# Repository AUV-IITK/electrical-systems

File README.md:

# electrical-systems
# PURPOSE
The boost converter is Dc to Dc step up volatage while stepping dowm current. It is mainly used to reduce the voltage ripples in the input side(battery) to produce constant Dc output.
# SPECS
- Input Voltage range-14.8 to 16.8 volts
- DC output-19 volts
- output current- 3A
- Ambient Temp-30degree Centigrade
- base_pn-TPS55340-Q1

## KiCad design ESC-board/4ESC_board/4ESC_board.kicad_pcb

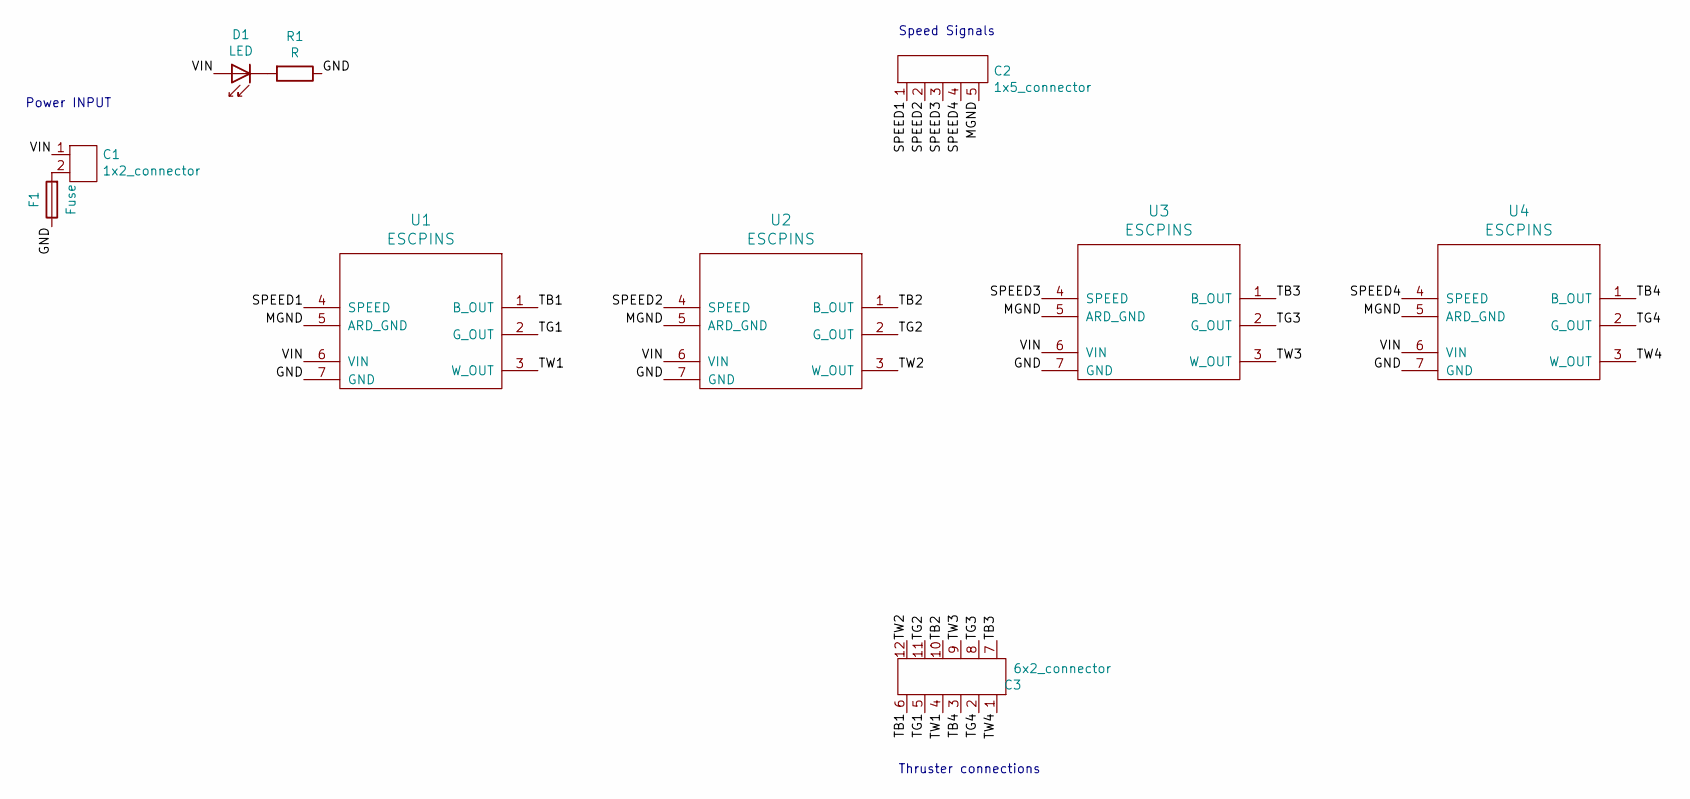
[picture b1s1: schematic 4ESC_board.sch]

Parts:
C1: 1x2_connector; molex_supersabre_1x2_172043-0201
C2: 1x5_connector; Molex_Microfit_1x5_436500500
C3: 6x2_connector; Molex_microfit_2x6_444281201
D1: LED; D_1206_3216Metric_Pad1.42x1.75mm_HandSolder
F1: Fuse; MCCQ-122
R1: R; R_1206_3216Metric_Pad1.42x1.75mm_HandSolder
U1, U2, U3, U4: ESCPINS; ESC_footprint

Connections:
/GND: F1.1, R1.1, U1.7 (GND), U2.7 (GND), U3.7 (GND), U4.7 (GND)
/MGND: C2.5, U1.5 (ARD_GND), U2.5 (ARD_GND), U3.5 (ARD_GND), U4.5 (ARD_GND)
/SPEED1: C2.1, U1.4 (SPEED)
/SPEED2: C2.2, U2.4 (SPEED)
/SPEED3: C2.3, U3.4 (SPEED)
/SPEED4: C2.4, U4.4 (SPEED)
/TB1: C3.6, U1.1 (B_OUT)
/TB2: C3.10, U2.1 (B_OUT)
/TB3: C3.7, U3.1 (B_OUT)
/TB4: C3.3, U4.1 (B_OUT)
/TG1: C3.5, U1.2 (G_OUT)
/TG2: C3.11, U2.2 (G_OUT)
/TG3: C3.8, U3.2 (G_OUT)
/TG4: C3.2, U4.2 (G_OUT)
/TW1: C3.4, U1.3 (W_OUT)
/TW2: C3.12, U2.3 (W_OUT)
/TW3: C3.9, U3.3 (W_OUT)
/TW4: C3.1, U4.3 (W_OUT)
/VIN: C1.1, D1.2 (A), U1.6 (VIN), U2.6 (VIN), U3.6 (VIN), U4.6 (VIN)
unnamed: C1.2, F1.2
unnamed: D1.1 (K), R1.2

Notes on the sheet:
Power INPUT
Speed Signals
Thruster connections

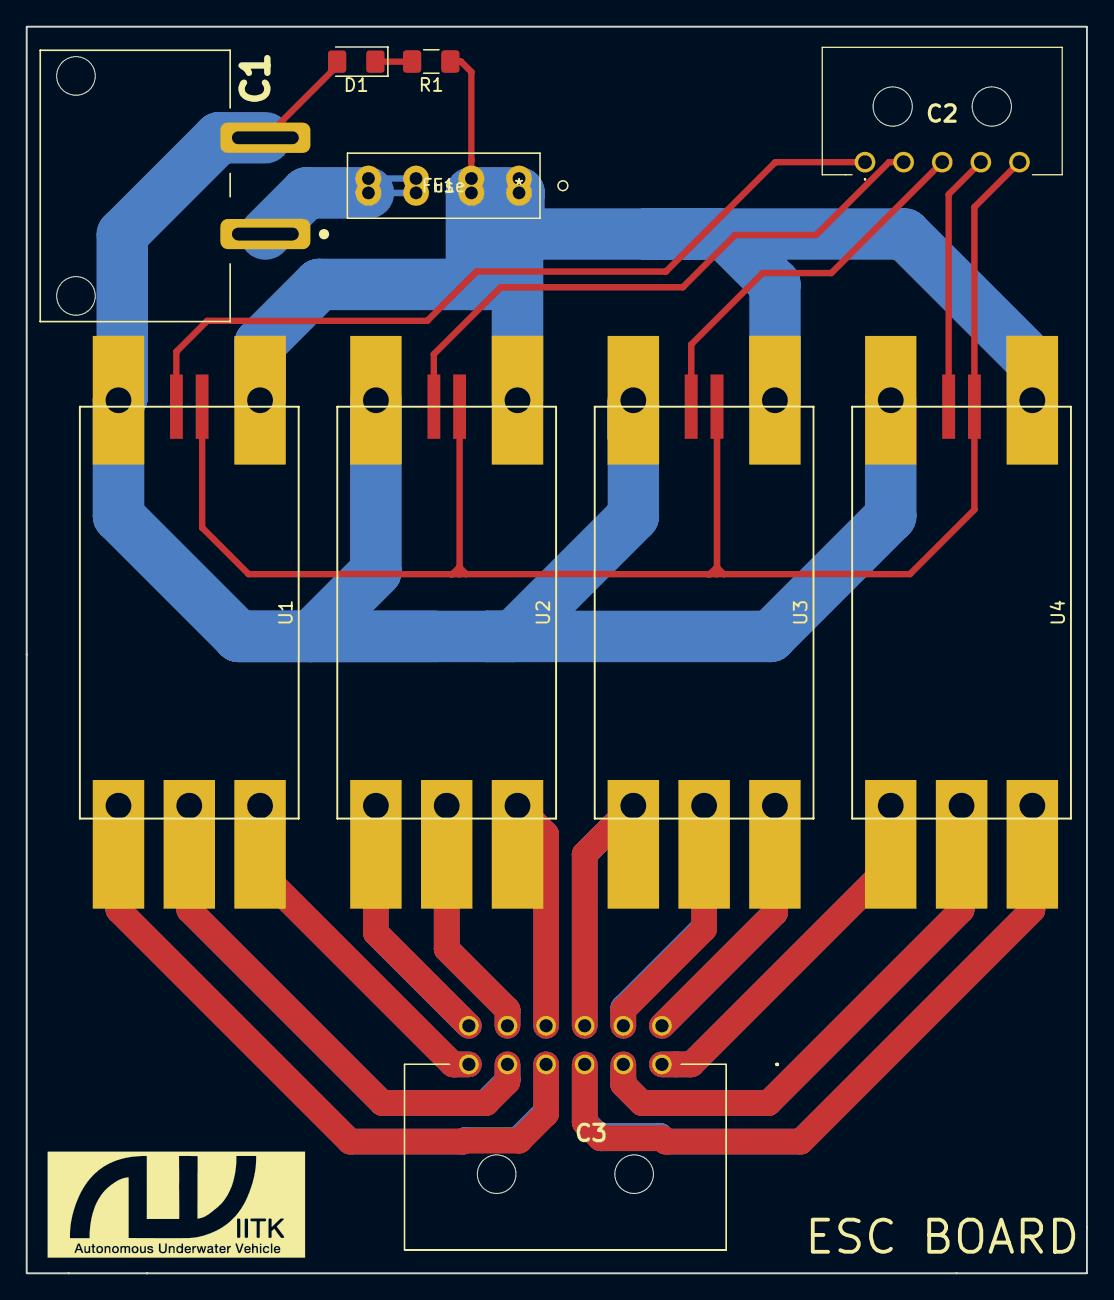
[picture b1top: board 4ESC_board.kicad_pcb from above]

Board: 2 copper layers, 82.4 x 96.9 mm, 10 parts (0 on the bottom side), 21 nets.

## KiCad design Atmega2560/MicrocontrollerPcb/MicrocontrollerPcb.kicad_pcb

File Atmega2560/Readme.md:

**This is the repository for ATMEGA 2560**

The files contains the scematic and the PCB layout done in KICAD and would be updated from time to time.

Updated schematic for PCB, added LED and linked footprints for various elements used in the circuit. Also added two folders for footprints usde in the circuit. **2560_Footprints** contains the files for predefined footprints available in KICAD. the other **Molex_Connector** contains the footprints of molex connectors to be used in the project.

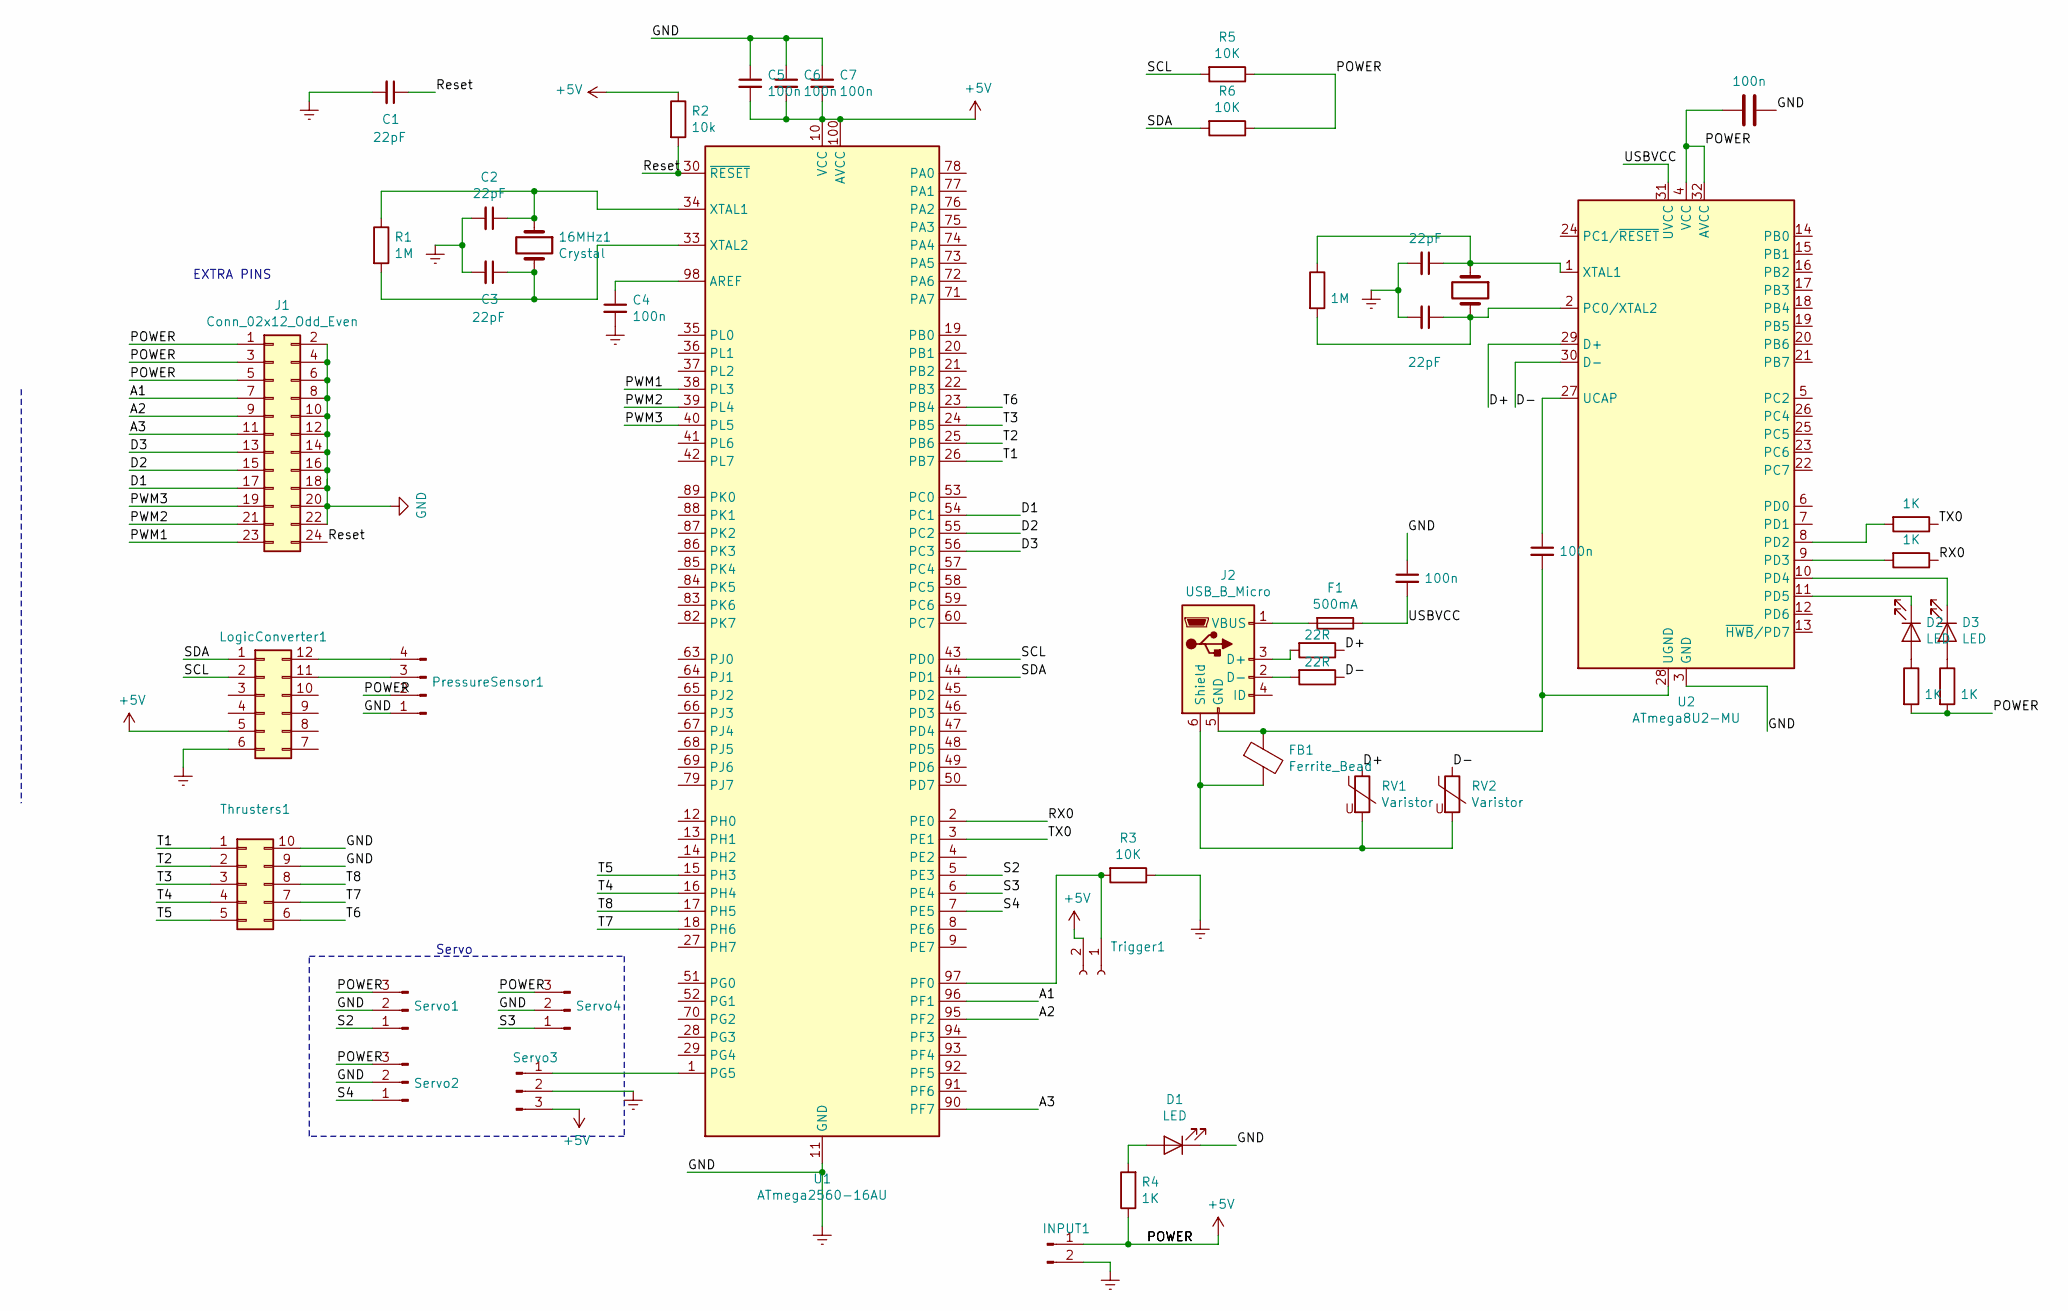
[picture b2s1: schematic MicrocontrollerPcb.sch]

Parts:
16MHz1, 16MHz2: Crystal; Crystal_HC49-U_Vertical
C1, C2, C3, C9, C10: 22pF; C_0805_2012Metric_Pad1.15x1.40mm_HandSolder
C4, C5, C6, C7, C8, C11, C12: 100n; C_0603_1608Metric_Pad1.05x0.95mm_HandSolder
D1, D2, D3: LED; LED_1206_3216Metric
F1: 500mA; Fuse_1206_3216Metric_Pad1.42x1.75mm_HandSolder
FB1: Ferrite_Bead; R_0805_2012Metric
INPUT1: Conn_01x02_Male; input
J1: Conn_02x12_Odd_Even; PinHeader_2x12_P2.54mm_Vertical
J2: USB_B_Micro; USB_Micro-B_Amphenol_10103594-0001LF_Horizontal
LogicConverter1: Conn_02x06_Counter_Clockwise; 02x06
PressureSensor1: Conn_01x04_Male; 53375-0410
R1, R7: 1M; R_0402_1005Metric
R2: 10k; R_0402_1005Metric
R3, R5, R6: 10K; R_0402_1005Metric
R4, R10, R11, R12, R13: 1K; R_1206_3216Metric_Pad1.42x1.75mm_HandSolder
R8, R9: 22R; R_0603_1608Metric_Pad1.05x0.95mm_HandSolder
RV1, RV2: Varistor; R_0603_1608Metric_Pad1.05x0.95mm_HandSolder
Servo1, Servo2, Servo3, Servo4: Conn_01x03_Male; 01x03
Thrusters1: Connector 02x05; 02x05
Trigger1: Conn_01x02_Female; 53375-0210
U1: ATmega2560-16AU; TQFP-100_14x14mm_P0.5mm
U2: ATmega8U2-MU; QFN-32-1EP_5x5mm_P0.5mm_EP3.1x3.1mm

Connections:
+5V: C5.2, C6.2, C7.2, C12.2, INPUT1.1, J1.1, J1.3, J1.5, LogicConverter1.5, PressureSensor1.2, R2.1, R4.1, R5.1, R6.1, R12.2, R13.2, Servo1.3, Servo2.3, Servo3.3, Servo4.3, Trigger1.2, U1.10 (VCC), U1.31 (VCC), U1.61 (VCC), U1.80 (VCC), U1.100 (AVCC), U2.4 (VCC), U2.32 (AVCC)
/A1: J1.7, U1.96 (PF1)
/A2: J1.9, U1.95 (PF2)
/A3: J1.11, U1.90 (PF7)
/D1: J1.17, U1.54 (PC1)
/D2: J1.15, U1.55 (PC2)
/D3: J1.13, U1.56 (PC3)
/D+: R8.1, RV1.1, U2.29 (D+)
/D-: R9.1, RV2.1, U2.30 (D-)
/PWM1: J1.23, U1.38 (PL3)
/PWM2: J1.21, U1.39 (PL4)
/PWM3: J1.19, U1.40 (PL5)
/RX0: R11.1, U1.2 (PE0)
/Reset: C1.1, J1.24, R2.2, U1.30 (~RESET)
/S2: Servo1.1, U1.5 (PE3)
/S3: Servo4.1, U1.6 (PE4)
/S4: Servo2.1, U1.7 (PE5)
/SCL: LogicConverter1.2, R5.2, U1.43 (PD0)
/SDA: LogicConverter1.1, R6.2, U1.44 (PD1)
/T1: Thrusters1.1, U1.26 (PB7)
/T2: Thrusters1.2, U1.25 (PB6)
/T3: Thrusters1.3, U1.24 (PB5)
/T4: Thrusters1.4, U1.16 (PH4)
/T5: Thrusters1.5, U1.15 (PH3)
/T6: Thrusters1.6, U1.23 (PB4)
/T7: Thrusters1.7, U1.18 (PH6)
/T8: Thrusters1.8, U1.17 (PH5)
/TX0: R10.1, U1.3 (PE1)
/USBVCC: C8.2, F1.1, U2.31 (UVCC)
Earth: C1.2, C2.2, C3.2, C4.2, C5.1, C6.1, C7.1, C8.1, C9.2, C10.2, C12.1, D1.1 (K), INPUT1.2, J1.2, J1.4, J1.6, J1.8, J1.10, J1.12, J1.14, J1.16, J1.18, J1.20, J1.22, LogicConverter1.6, PressureSensor1.1, R3.1, Servo1.2, Servo2.2, Servo3.2, Servo4.2, Thrusters1.9, Thrusters1.10, U1.11 (GND), U1.32 (GND), U1.62 (GND), U1.81 (GND), U1.99 (GND), U2.3 (GND), U2.33 (GND)
unnamed: 16MHz1.1, C2.1, R1.1, U1.34 (XTAL1)
unnamed: 16MHz1.2, C3.1, R1.2, U1.33 (XTAL2)
unnamed: 16MHz2.1, C9.1, R7.1, U2.1 (XTAL1)
unnamed: 16MHz2.2, C10.1, R7.2, U2.2 (PC0/XTAL2)
unnamed: C4.1, U1.98 (AREF)
unnamed: C11.1, U2.27 (UCAP)
unnamed: C11.2, FB1.1, J2.5 (GND), U2.28 (UGND)
unnamed: D1.2 (A), R4.2
unnamed: D2.1 (K), U2.11 (PD5)
unnamed: D2.2 (A), R12.1
unnamed: D3.1 (K), U2.10 (PD4)
unnamed: D3.2 (A), R13.1
unnamed: F1.2, J2.1 (VBUS)
unnamed: FB1.2, J2.6 (Shield), RV1.2, RV2.2
unnamed: J2.2 (D-), R9.2
unnamed: J2.3 (D+), R8.2
unnamed: LogicConverter1.11, PressureSensor1.3
unnamed: LogicConverter1.12, PressureSensor1.4
unnamed: R3.2, Trigger1.1, U1.97 (PF0)
unnamed: R10.2, U2.8 (PD2)
unnamed: R11.2, U2.9 (PD3)
unnamed: Servo3.1, U1.1 (PG5)

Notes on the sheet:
EXTRA PINS
Servo

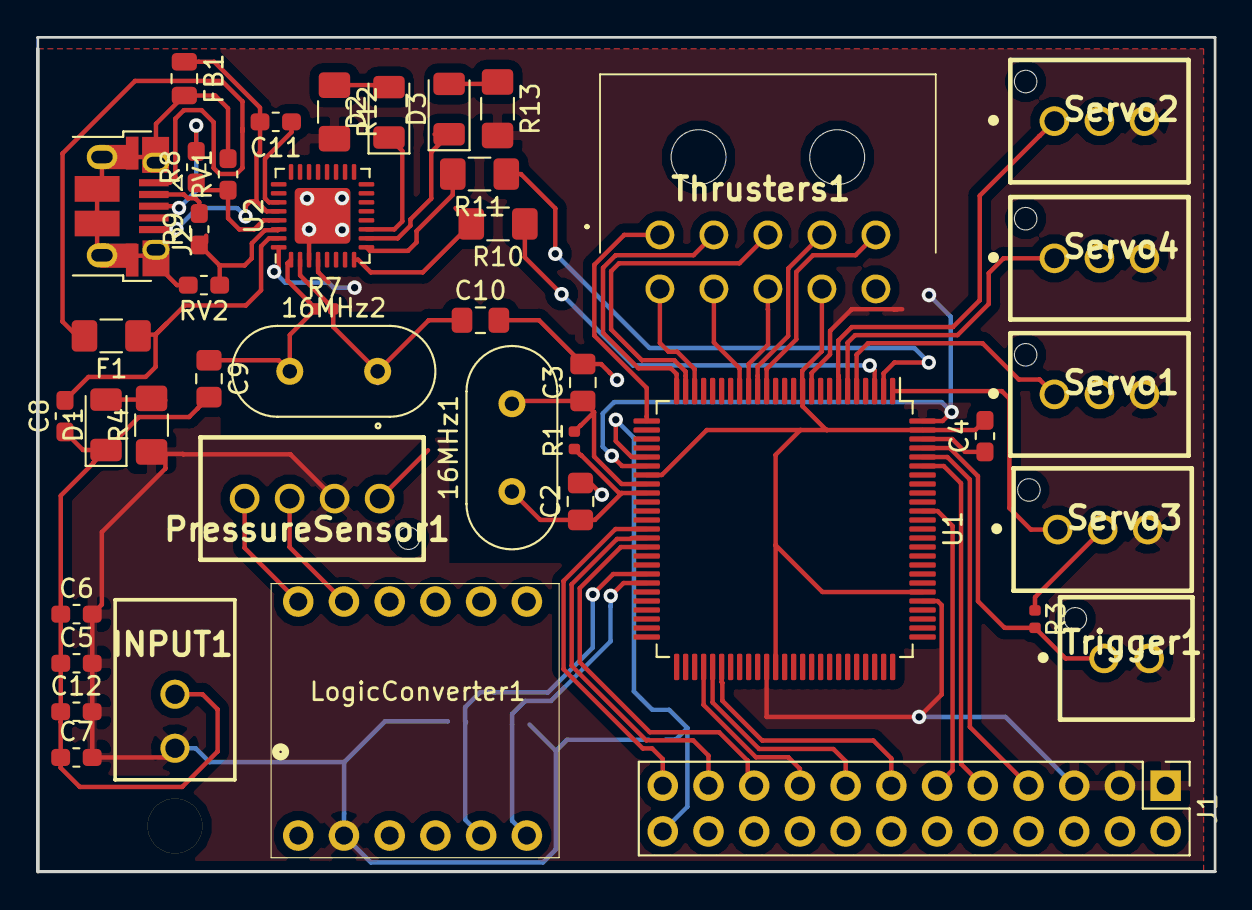
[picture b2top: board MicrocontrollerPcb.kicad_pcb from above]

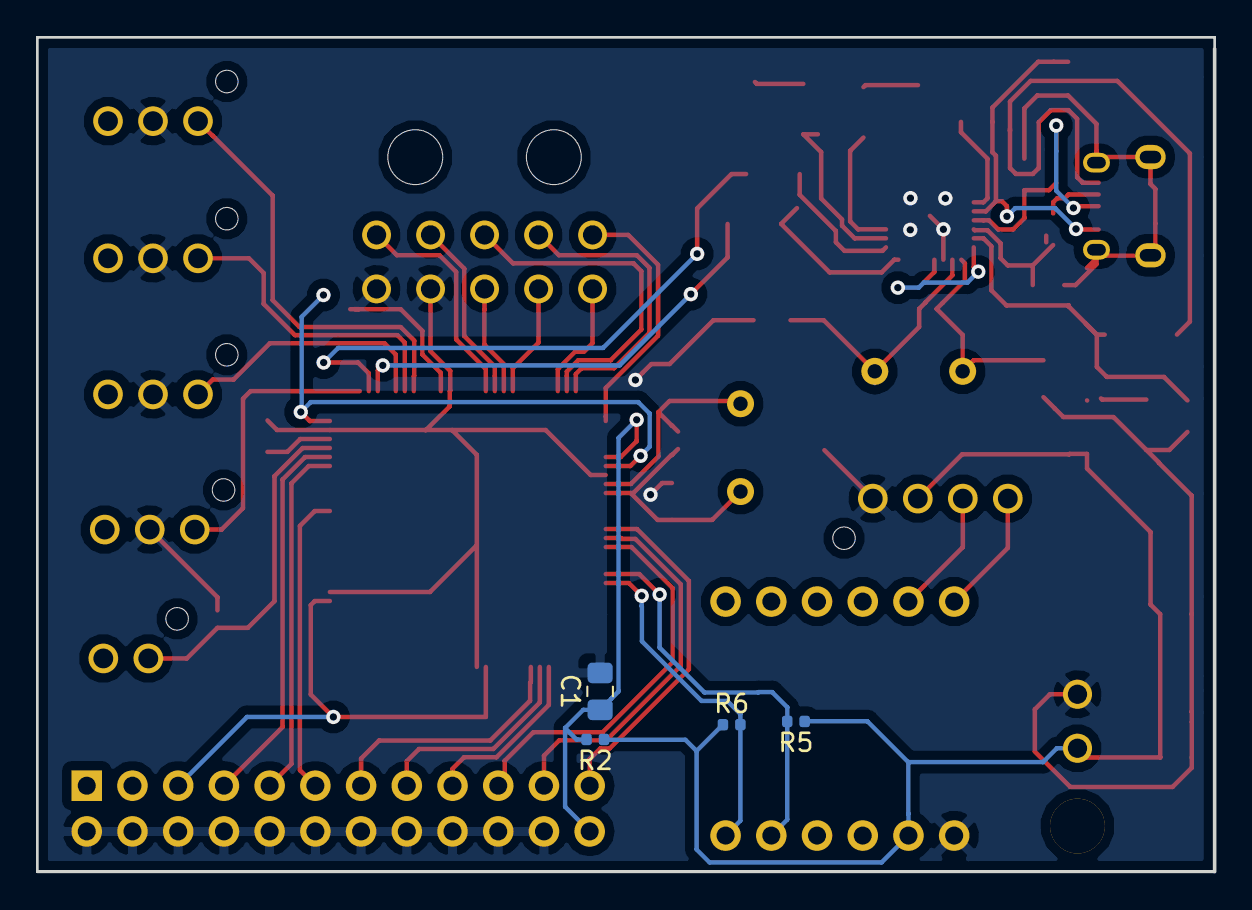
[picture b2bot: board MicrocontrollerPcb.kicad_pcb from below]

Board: 2 copper layers, 65.4 x 46.4 mm, 47 parts (4 on the bottom side), 52 nets.

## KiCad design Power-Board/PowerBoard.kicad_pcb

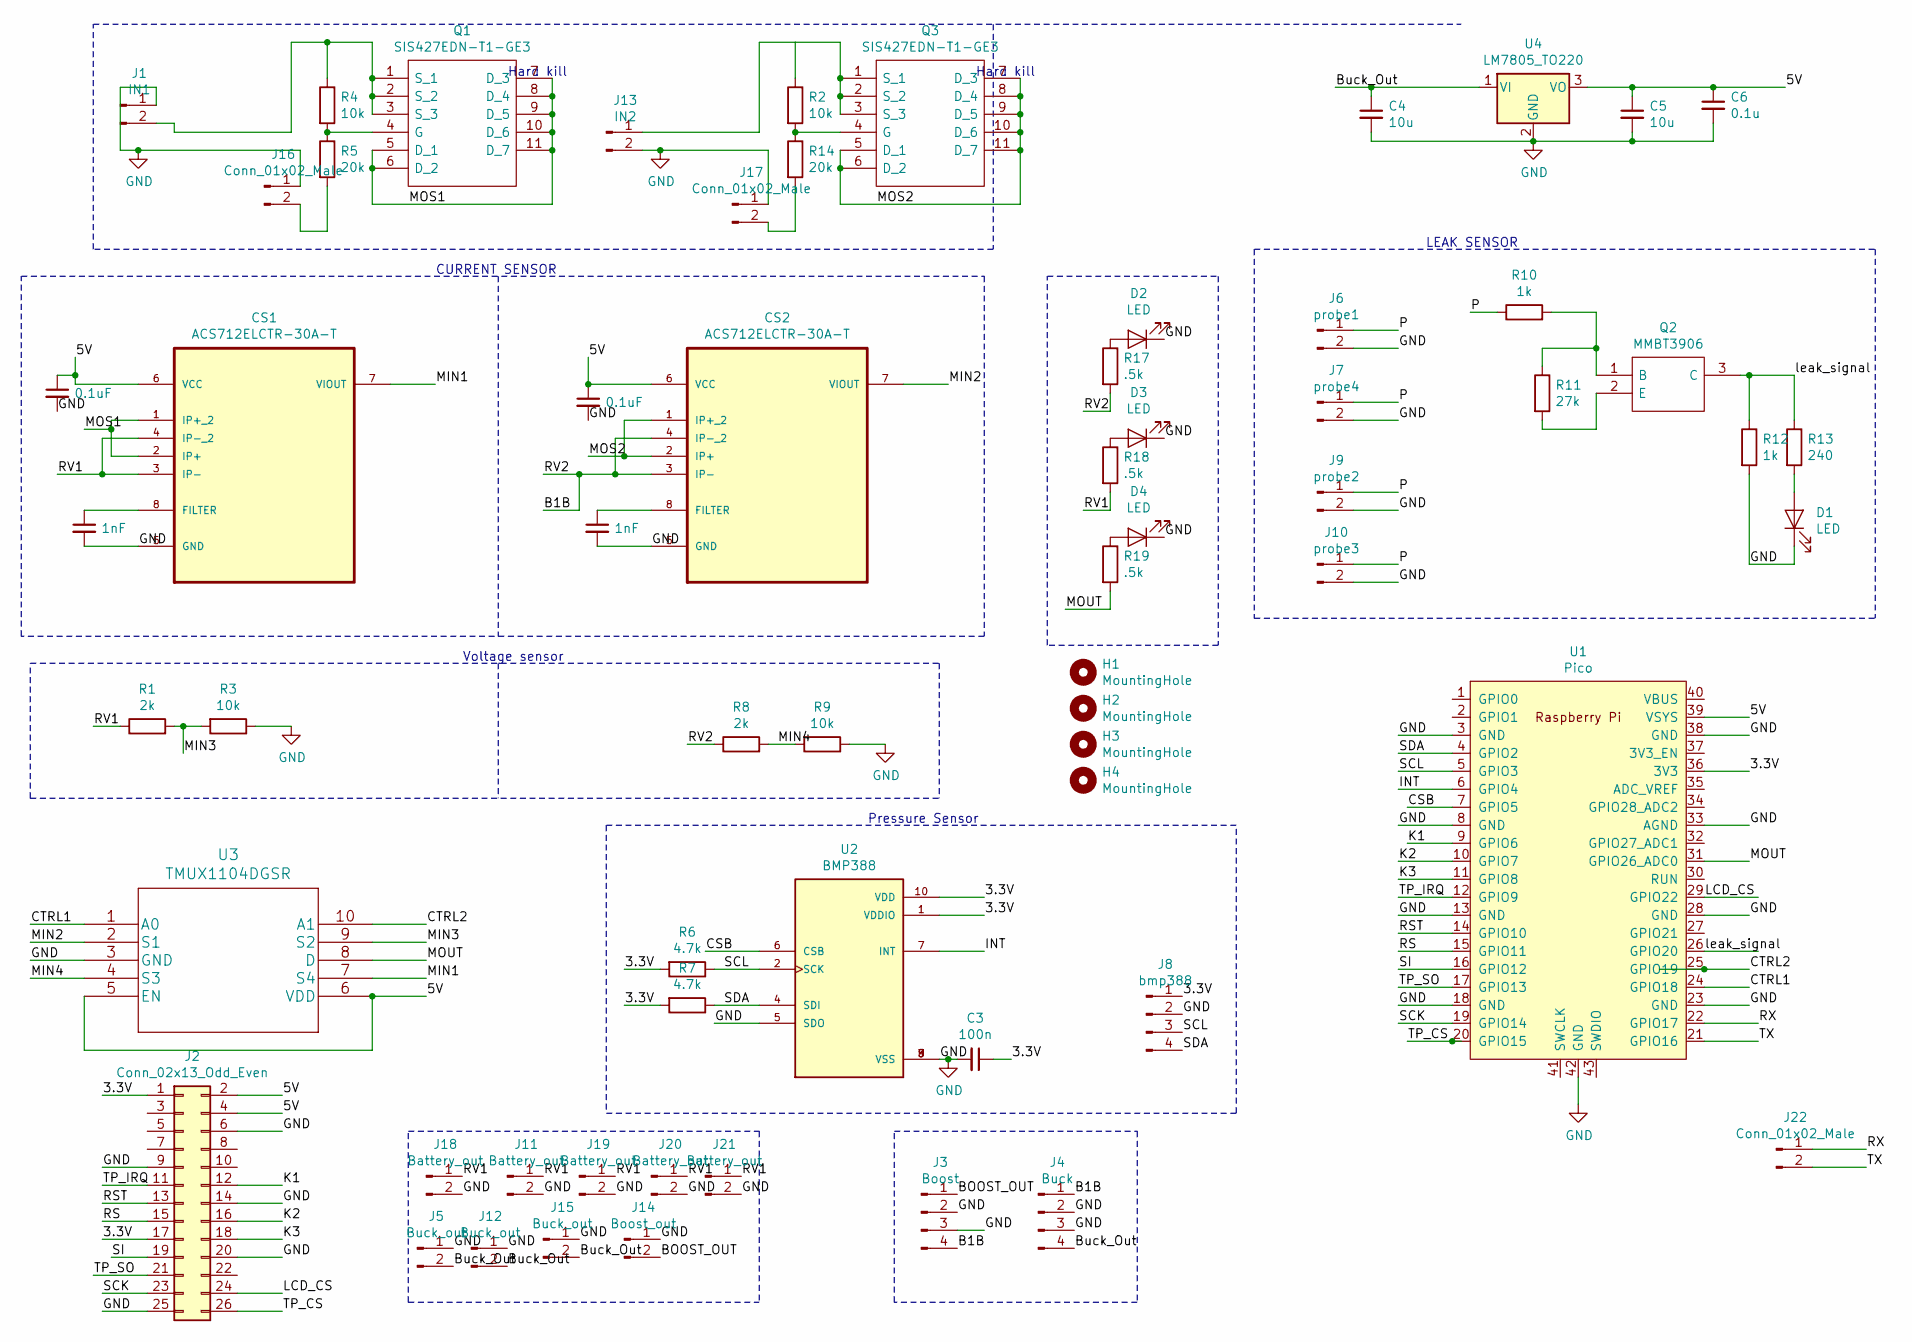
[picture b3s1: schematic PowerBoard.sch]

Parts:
C1, C8: 1nF; C_0603_1608Metric_Pad1.05x0.95mm_HandSolder
C2, C7: 0.1uF; C_0603_1608Metric_Pad1.05x0.95mm_HandSolder
C3: 100n; C_0603_1608Metric_Pad1.05x0.95mm_HandSolder
C4, C5: 10u; C_0603_1608Metric_Pad1.05x0.95mm_HandSolder
C6: 0.1u; C_0603_1608Metric_Pad1.05x0.95mm_HandSolder
CS1, CS2: ACS712ELCTR-30A-T; SOIC127P600X175-8N
D1, D2, D3, D4: LED; LED_0603_1608Metric
H1, H2, H3, H4: MountingHole; MountingHole_3.2mm_M3
J1: IN1; molex_supersabre_1x2_172043-0201
J2: Conn_02x13_Odd_Even; PinHeader_2x13_P2.54mm_Vertical
J3: Boost; CON_436500400_MOL
J4: Buck; CON_436500400_MOL
J5, J12, J15: Buck_out; input
J6: probe1; 01x02
J7: probe4; 01x02
J8: bmp388; PinHeader_1x04_P2.54mm_Vertical
J9: probe2; 01x02
J10: probe3; 01x02
J11: Battery_out; molex_supersabre_1x2_172043-0201
J13: IN2; molex_supersabre_1x2_172043-0201
J14: Boost_out; input
J16, J17, J22: Conn_01x02_Male; 01x02
J18, J19, J20, J21: Battery_out; input
Q1, Q3: SIS427EDN-T1-GE3; SIS862DNT1GE3; Mouser Part Number 78-SIS427EDN-T1-GE3
Q2: MMBT3906; SOT95P240X120-3N; Mouser Part Number 512-MMBT3906
R1, R8: 2k; R_0603_1608Metric_Pad1.05x0.95mm_HandSolder
R2, R3, R4, R9: 10k; R_0603_1608Metric_Pad1.05x0.95mm_HandSolder
R5, R14: 20k; R_0603_1608Metric_Pad1.05x0.95mm_HandSolder
R6, R7: 4.7k; R_0603_1608Metric_Pad1.05x0.95mm_HandSolder
R10, R12: 1k; R_0603_1608Metric_Pad1.05x0.95mm_HandSolder
R11: 27k; R_0603_1608Metric_Pad1.05x0.95mm_HandSolder
R13: 240; R_0805_2012Metric_Pad1.15x1.40mm_HandSolder
R17, R18, R19: .5k; R_0603_1608Metric_Pad1.05x0.95mm_HandSolder
U1: Pico; RPi_Pico_SMD_TH
U2: BMP388; PQFN50P200X200X80-10N; PARTREV 1.1
U3: TMUX1104DGSR; DGS10_TEX
U4: LM7805_TO220; TO-220-3_Vertical

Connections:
/3.3V: C3.1, J2.1, J2.17, J8.1, R6.2, R7.2, U1.36 (3V3), U2.1 (VDDIO), U2.10 (VDD)
/5V: C2.1, C5.1, C6.1, C7.1, CS1.6 (VCC), CS2.6 (VCC), J2.2, J2.4, U1.39 (VSYS), U3.5 (EN), U3.6 (VDD), U4.3 (VO)
/B1B: CS2.3 (IP-), CS2.4 (IP-_2), J3.4, J4.1, R8.1, R17.2
/BOOST_OUT: J3.1, J14.2
/Buck_Out: C4.1, J4.4, J5.2, J12.2, J15.2, U4.1 (VI)
/CSB: U1.7 (GPIO5), U2.6 (CSB)
/CTRL1: U1.24 (GPIO18), U3.1 (A0)
/CTRL2: U1.25 (GPIO19), U3.10 (A1)
/INT: U1.6 (GPIO4), U2.7 (INT)
/K1: J2.12, U1.9 (GPIO6)
/K2: J2.16, U1.10 (GPIO7)
/K3: J2.18, U1.11 (GPIO8)
/LCD_CS: J2.24, U1.29 (GPIO22)
/MIN1: CS1.7 (VIOUT), U3.7 (S4)
/MIN2: CS2.7 (VIOUT), U3.2 (S1)
/MIN3: R1.2, R3.2, U3.9 (S2)
/MIN4: R8.2, R9.2, U3.4 (S3)
/MOS1: CS1.1 (IP+_2), CS1.2 (IP+), Q1.5 (D_1), Q1.6 (D_2), Q1.7 (D_3), Q1.8 (D_4), Q1.9 (D_5), Q1.10 (D_6), Q1.11 (D_7)
/MOS2: CS2.1 (IP+_2), CS2.2 (IP+), Q3.5 (D_1), Q3.6 (D_2), Q3.7 (D_3), Q3.8 (D_4), Q3.9 (D_5), Q3.10 (D_6), Q3.11 (D_7)
/MOUT: R19.2, U1.31 (GPIO26_ADC0), U3.8 (D)
/P: J6.1, J7.1, J9.1, J10.1, R10.1
/RS: J2.15, U1.15 (GPIO11)
/RST: J2.13, U1.14 (GPIO10)
/RV1: CS1.3 (IP-), CS1.4 (IP-_2), J11.1, J18.1, J19.1, J20.1, J21.1, R1.1, R18.2
/RX: J22.1, U1.22 (GPIO17)
/SCK: J2.23, U1.19 (GPIO14)
/SCL: J8.3, R6.1, U1.5 (GPIO3), U2.2 (SCK)
/SDA: J8.4, R7.1, U1.4 (GPIO2), U2.4 (SDI)
/SI: J2.19, U1.16 (GPIO12)
/TP_CS: J2.26, U1.20 (GPIO15)
/TP_IRQ: J2.11, U1.12 (GPIO9)
/TP_SO: J2.21, U1.17 (GPIO13)
/TX: J22.2, U1.21 (GPIO16)
/leak_signal: Q2.3 (C), R12.1, R13.1, U1.26 (GPIO20)
GND: C1.2, C2.2, C3.2, C4.2, C5.2, C6.2, C7.2, C8.2, CS1.5 (GND), CS2.5 (GND), D1.1 (K), D2.1 (K), D3.1 (K), D4.1 (K), J1.1, J2.6, J2.9, J2.14, J2.20, J2.25, J3.2, J3.3, J4.2, J4.3, J5.1, J6.2, J7.2, J8.2, J9.2, J10.2, J11.2, J12.1, J13.2, J14.1, J15.1, J16.1, J17.1, J18.2, J19.2, J20.2, J21.2, R3.1, R9.1, R12.2, U1.3 (GND), U1.8 (GND), U1.13 (GND), U1.18 (GND), U1.23 (GND), U1.28 (GND), U1.33 (AGND), U1.38 (GND), U1.42 (GND), U2.3 (VSS), U2.5 (SDO), U2.8 (VSS), U2.9 (VSS), U3.3 (GND), U4.2 (GND)
unnamed: C1.1, CS1.8 (FILTER)
unnamed: C8.1, CS2.8 (FILTER)
unnamed: D1.2 (A), R13.2
unnamed: D2.2 (A), R17.1
unnamed: D3.2 (A), R18.1
unnamed: D4.2 (A), R19.1
unnamed: J1.2, Q1.1 (S_1), Q1.2 (S_2), Q1.3 (S_3), R4.1
unnamed: J13.1, Q3.1 (S_1), Q3.2 (S_2), Q3.3 (S_3), R2.1
unnamed: J16.2, R5.2
unnamed: J17.2, R14.2
unnamed: Q1.4 (G), R4.2, R5.1
unnamed: Q2.1 (B), R10.2, R11.1
unnamed: Q2.2 (E), R11.2
unnamed: Q3.4 (G), R2.2, R14.1

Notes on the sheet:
Hard kill
CURRENT SENSOR
Voltage sensor
Pressure Sensor
LEAK SENSOR

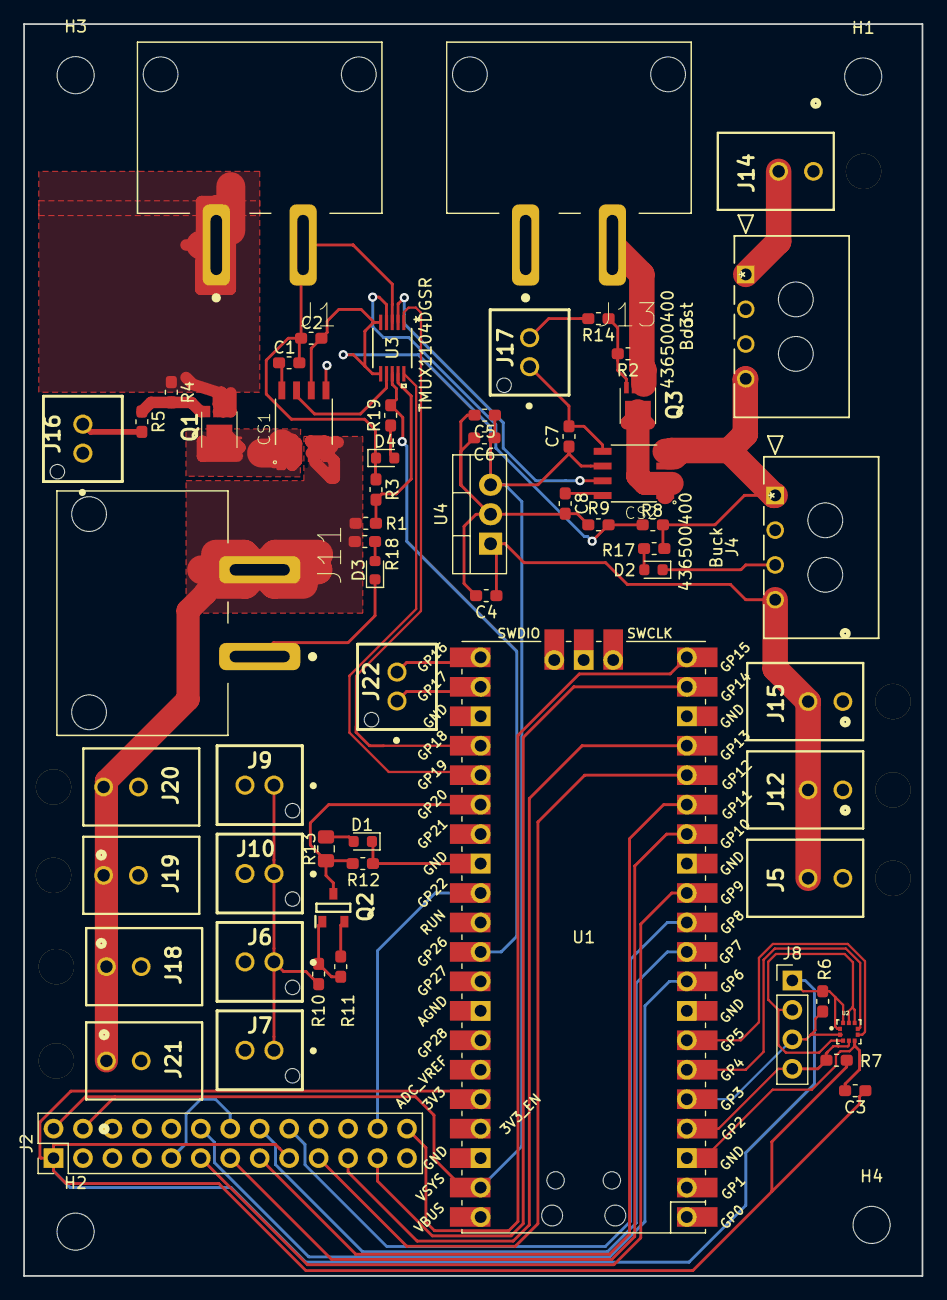
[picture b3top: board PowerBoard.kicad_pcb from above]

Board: 2 copper layers, 77.5 x 107.9 mm, 64 parts (0 on the bottom side), 49 nets.

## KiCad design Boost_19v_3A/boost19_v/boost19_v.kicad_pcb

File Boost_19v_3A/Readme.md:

# Boost Converter for the NUC

 The simulation has been run on TINA-TI Spice software. Download from here [Link](http://www.ti.com/tool/TINA-TI).

 Results of a simulation on the [Webench](https://webench.ti.com/power-designer/) have been placed in the in the simulation output folder. 

 To run simulation download the schematic and open with TINA-TI.

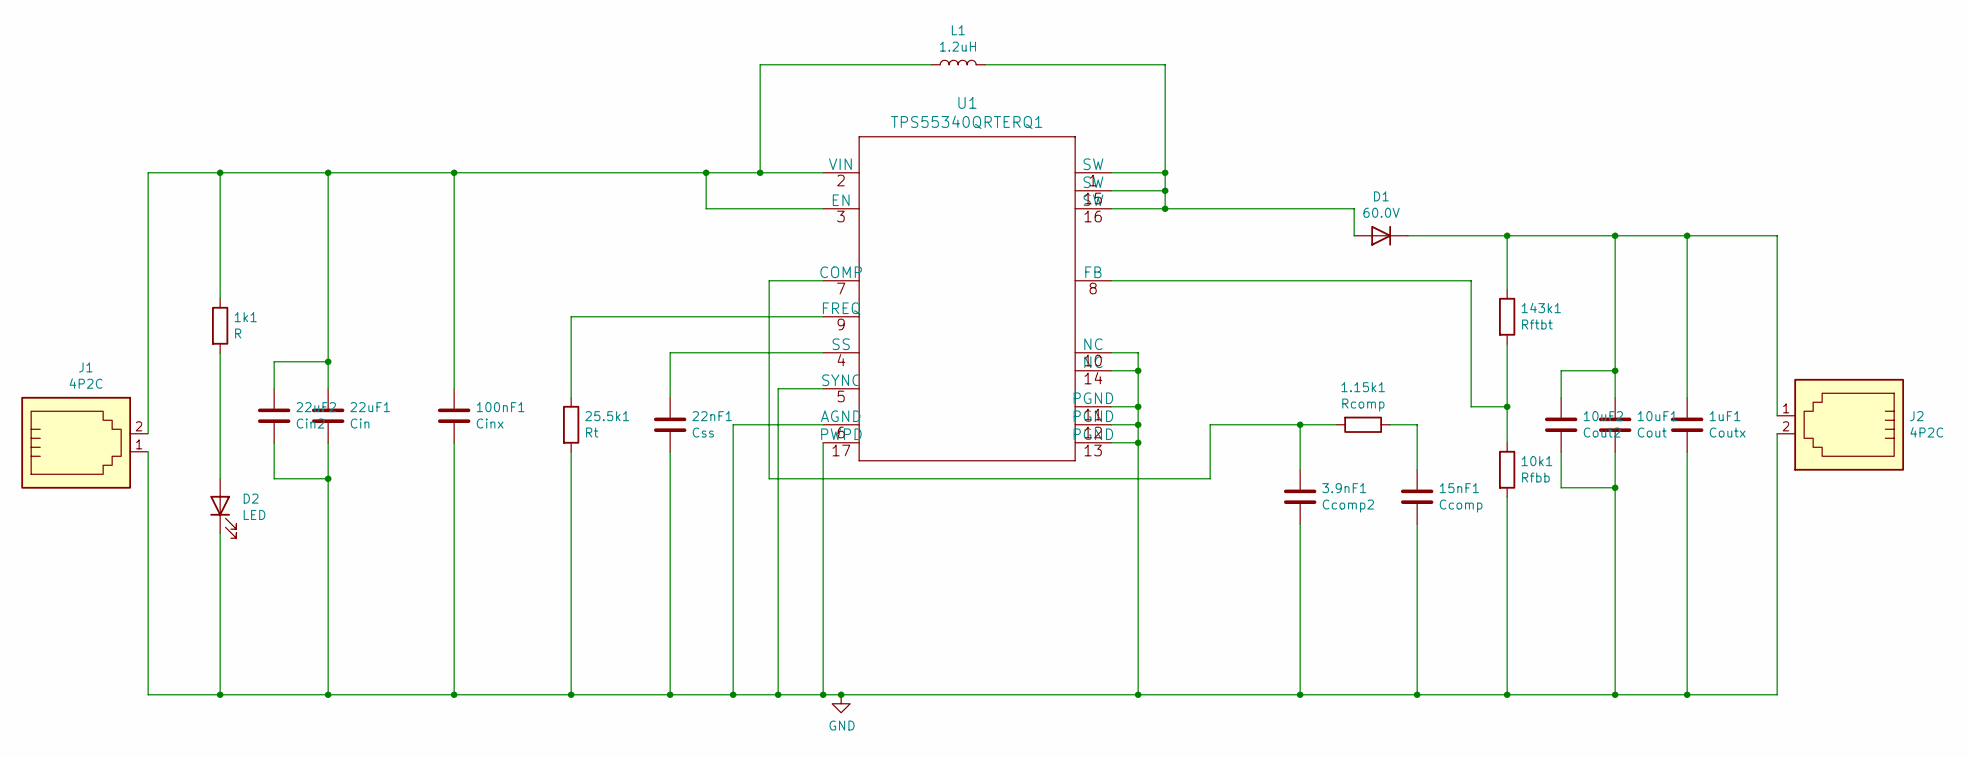
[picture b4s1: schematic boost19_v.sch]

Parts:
1.15k1: Rcomp; R_0402_1005Metric_Pad0.72x0.64mm_HandSolder
1k1: R; R_1206_3216Metric_Pad1.30x1.75mm_HandSolder
1uF1: Coutx; C_0805_2012Metric_Pad1.18x1.45mm_HandSolder
3.9nF1: Ccomp2; C_0201_0603Metric_Pad0.64x0.40mm_HandSolder
10k1: Rfbb; R_0201_0603Metric_Pad0.64x0.40mm_HandSolder
10uF1: Cout; C_1210_3225Metric_Pad1.33x2.70mm_HandSolder
10uF2: Cout2; C_1210_3225Metric_Pad1.33x2.70mm_HandSolder
15nF1: Ccomp; C_0201_0603Metric_Pad0.64x0.40mm_HandSolder
22nF1: Css; C_0402_1005Metric_Pad0.74x0.62mm_HandSolder
22uF1: Cin; C_0805_2012Metric_Pad1.18x1.45mm_HandSolder
22uF2: Cin2; C_0805_2012Metric_Pad1.18x1.45mm_HandSolder
25.5k1: Rt; R_0402_1005Metric_Pad0.72x0.64mm_HandSolder
100nF1: Cinx; C_0402_1005Metric_Pad0.74x0.62mm_HandSolder
143k1: Rftbt; R_0402_1005Metric_Pad0.72x0.64mm_HandSolder
D1: 60.0V; D_PowerDI-5
D2: LED; LED_1206_3216Metric_Pad1.42x1.75mm_HandSolder
J1, J2: 4P2C; 43045-0200
L1: 1.2uH; L_Wuerth_MAPI-4030
U1: TPS55340QRTERQ1

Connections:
GND: 1uF1.2, 3.9nF1.2, 10k1.2, 10uF1.2, 10uF2.2, 15nF1.2, 22nF1.2, 22uF1.2, 22uF2.2, 25.5k1.2, 100nF1.2, D2.1 (K), J1.1, J2.2, U1.5 (SYNC), U1.6 (AGND), U1.10 (NC), U1.11 (PGND), U1.12 (PGND), U1.13 (PGND), U1.14 (NC), U1.17 (PWPD)
unnamed: 1.15k1.1, 15nF1.1
unnamed: 1.15k1.2, 3.9nF1.1, U1.7 (COMP)
unnamed: 1k1.2, D2.2 (A)
unnamed: 10k1.1, 143k1.2, U1.8 (FB)
unnamed: 1uF1.1, 10uF1.1, 10uF2.1, 143k1.1, D1.1 (K), J2.1
unnamed: 22nF1.1, U1.4 (SS)
unnamed: 25.5k1.1, U1.9 (FREQ)
unnamed: 1k1.1, 22uF1.1, 22uF2.1, 100nF1.1, J1.2, L1.1, U1.2 (VIN), U1.3 (EN)
unnamed: D1.2 (A), L1.2, U1.1 (SW), U1.15 (SW), U1.16 (SW)

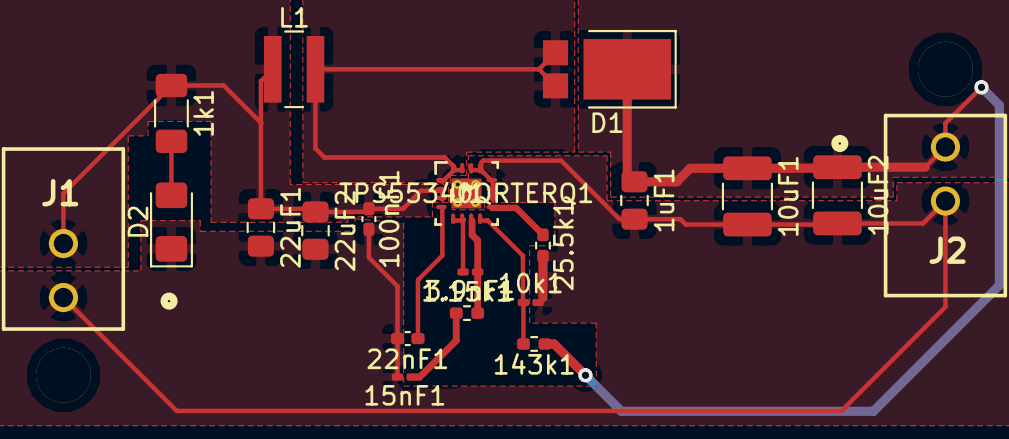
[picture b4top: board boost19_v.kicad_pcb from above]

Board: 2 copper layers, 20 parts (0 on the bottom side), 10 nets.

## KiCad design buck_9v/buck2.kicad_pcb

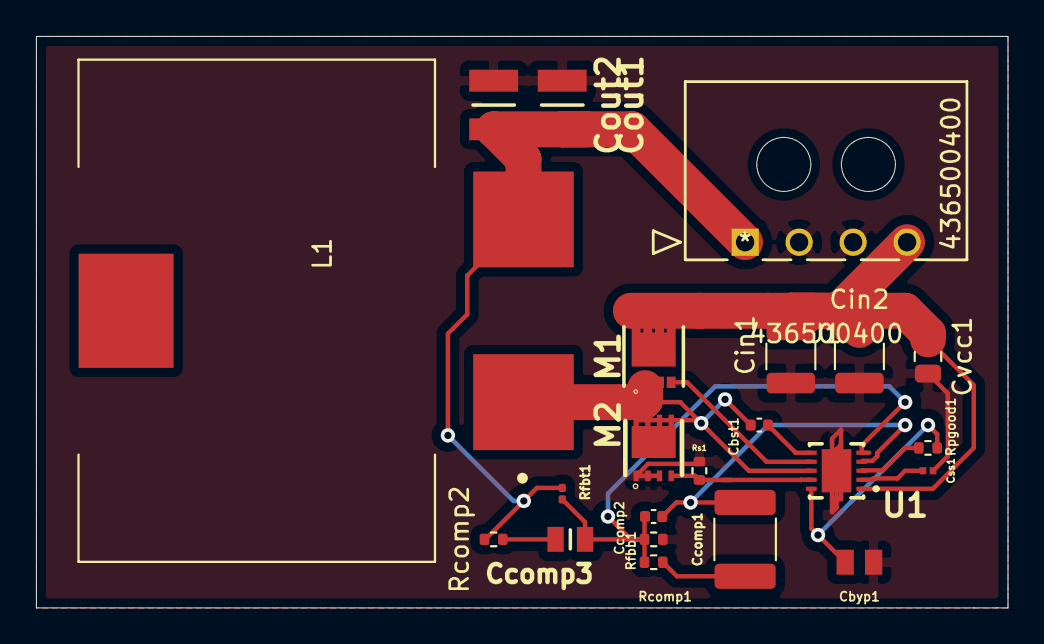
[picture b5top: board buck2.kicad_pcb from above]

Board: 2 copper layers, 54.0 x 31.8 mm, 22 parts (0 on the bottom side), 14 nets.

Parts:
Cbst1: 100nF,1mOhm; C_0402_1005Metric
Cbyp1: 2.2uF,1mOhm; CAPC2012X135N
Ccomp1: 18nF,0Ohm; C_1812_4532Metric
Ccomp2: 330pF,1mOhm; C_0402_1005Metric
Ccomp3: 4.7nF,0Ohm; CAPC2012X75N
Cin1, Cin2: 10uF,1mOhm; C_1210_3225Metric
Cout1, Cout2: 22uF,1mOhm; CAPC3225X270N
Css1: 3.3nF,1mOhm; CAPC0603X33N
Cvcc1: 1uF,1mOhm; C_0805_2012Metric
J1: 436500400
L1: SER2915L-223KL; IND_SER2915L-223KL
M1: 30V,56Amps; DQG_VSON-CLIP
M2: 30V,35Amps; Q3A
Rcomp1: 2.43kOhm; R_0402_1005Metric
Rcomp2: 191Ohm; R_0402_1005Metric
Rfbb1: 715Ohm; R_0402_1005Metric
Rfbt1: 10kOhm; R_0201_0603Metric
Rpgood1: 100kOhm; R_0402_1005Metric
Rs1: 1.87kOhm; R_0402_1005Metric
U1: TPS40303DRCR

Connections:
FB-1: Ccomp2.2, Ccomp3.2, Rcomp1.2, Rfbb1.1, Rfbt1.2, U1.5
unnamed: Cbst1.1, U1.6
unnamed: Cbst1.2, L1.1, M1.1, M1.2, M1.3, M2.5, M2.6, M2.7, M2.8, U1.8
unnamed: Cbyp1.1, Rpgood1.2, U1.10
unnamed: Ccomp1.1, Rcomp1.1
unnamed: Ccomp1.2, Ccomp2.1, U1.4
unnamed: Ccomp3.1, Rcomp2.2
unnamed: Css1.1, U1.2
unnamed: M1.4, U1.7
unnamed: M2.4, Rs1.1, U1.9
unnamed: Rpgood1.1, U1.3
Vin1: Cin1.1, Cin2.1, Cvcc1.2, J1.4, M1.5, M1.6, M1.7, M1.8, U1.1
Vin2: Cbyp1.2, Cin1.2, Cin2.2, Cout1.1, Cout2.1, Css1.2, Cvcc1.1, J1.2, J1.3, M2.1, M2.2, M2.3, Rfbb1.2, Rs1.2, U1.11, U1.12, U1.13, U1.14, U1.15
Vout1: Cout1.2, Cout2.2, J1.1, L1.2, Rcomp2.1, Rfbt1.1

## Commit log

2020-04-30 starting repo
2020-04-30 starting repository
2020-04-30 boost converter details
    Added the details and things I found about the boost converter design.
2020-04-30 spliting branch Boost_19v_3A
2020-04-30 spliting branch_Buck_5v_5A
2020-04-30 Revert "spliting branch_Buck_5v_5A"
2020-04-30 restructuring repo
2020-04-30 made branch Boost
2020-04-30 made branch Buck_5-12v
2020-04-30 made branch MCU-Atmega2560
2020-04-30 made branch MCU-Atmega328p
2020-04-30 made branch Electrical-cad
2020-04-30 adding readme to master
2020-04-30 uploading readme file
2020-04-30 uploading readme
2020-04-30 boost_converter_update_01
    Added details about boost covnerter
2020-04-30 boost_converter_update_02
    removed the folders added accidentally
2020-04-30 Revert "Added Boost Converter Details"
2020-04-30 boost_converter_update_01
    Updated the details for the boost converter.
2020-04-30 Boost 19v (#13)
    * boost_converter_update_01
    Added details about boost covnerter
    * Revert "Added Boost Converter Details"
2020-04-30 Revert "Boost 19v (#13)"
    This reverts commit 8f394a97cebce2581ee2f1021dbb35846115baae.
2020-04-30 rebuilded repo
2020-04-30 rebuilded branch
2020-05-09 updating instructions
2020-05-10 Update Boost_19v
    Added the details about the TI-TINA model for the bost converter.
2020-09-05 organising branch Atmega2560
2020-11-17 New commit altogether, ignore previous
2020-11-28 Completed PCB Layout changed Input Connector footprint
2020-12-25 self
2020-12-28 Changed component Inductor->Fuse
2020-12-28 schematic completed
2020-12-30 PCBlayout, Routing, 3DModels, DONE
2020-12-30 logo-png changed
2021-01-10 Removed Trace error
2021-01-17 Create PCB
2021-01-17 Create kicad,sch
2021-01-17 boost converter schematic
2021-01-19 adding Kill_switch_board
2021-01-28 netlist of boost converter
2021-01-28 footprints of boost converter
2021-01-30 project files
2021-01-30 fp-lib table
2021-05-22 new board
2021-05-24 issues resolved
2021-05-24 boost 19_V complete board
2021-05-25 resistance values added to LED
2021-05-25 BMP issue resolved
2021-05-27 boost19v pcb layout updated
2021-05-27 Readme.md update
2021-05-28 boost 19v
2021-05-28 boost19v
2021-05-28 .brd file
2021-06-04 Initiated the PCB layout."
2021-06-04 Adding buck
2021-06-05 Aiwaye
2021-06-06 minor fixes, size reduced
2021-06-06 Intermediate PCB layout completed.
2021-06-07 Power Board completed
2021-06-08 issue resolved
2021-06-08 Added 3D models
2021-06-09 updated power-board and stp file
2021-06-09 Changed the mosfet simulation
2021-06-10 reorganising
2022-03-16 power-trace plane changed, gerber-BOM generated
2022-03-17 added fuse
2023-04-13 Added a Documentation folder
2023-04-15 Hydrophones Testing Vi added
2023-04-15 More docs added

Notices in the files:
parts and their libraries:
Copyright 2016 Accelerated Designs. All rights reserved.
Copyright 2021 Accelerated Designs. All rights reserved.
